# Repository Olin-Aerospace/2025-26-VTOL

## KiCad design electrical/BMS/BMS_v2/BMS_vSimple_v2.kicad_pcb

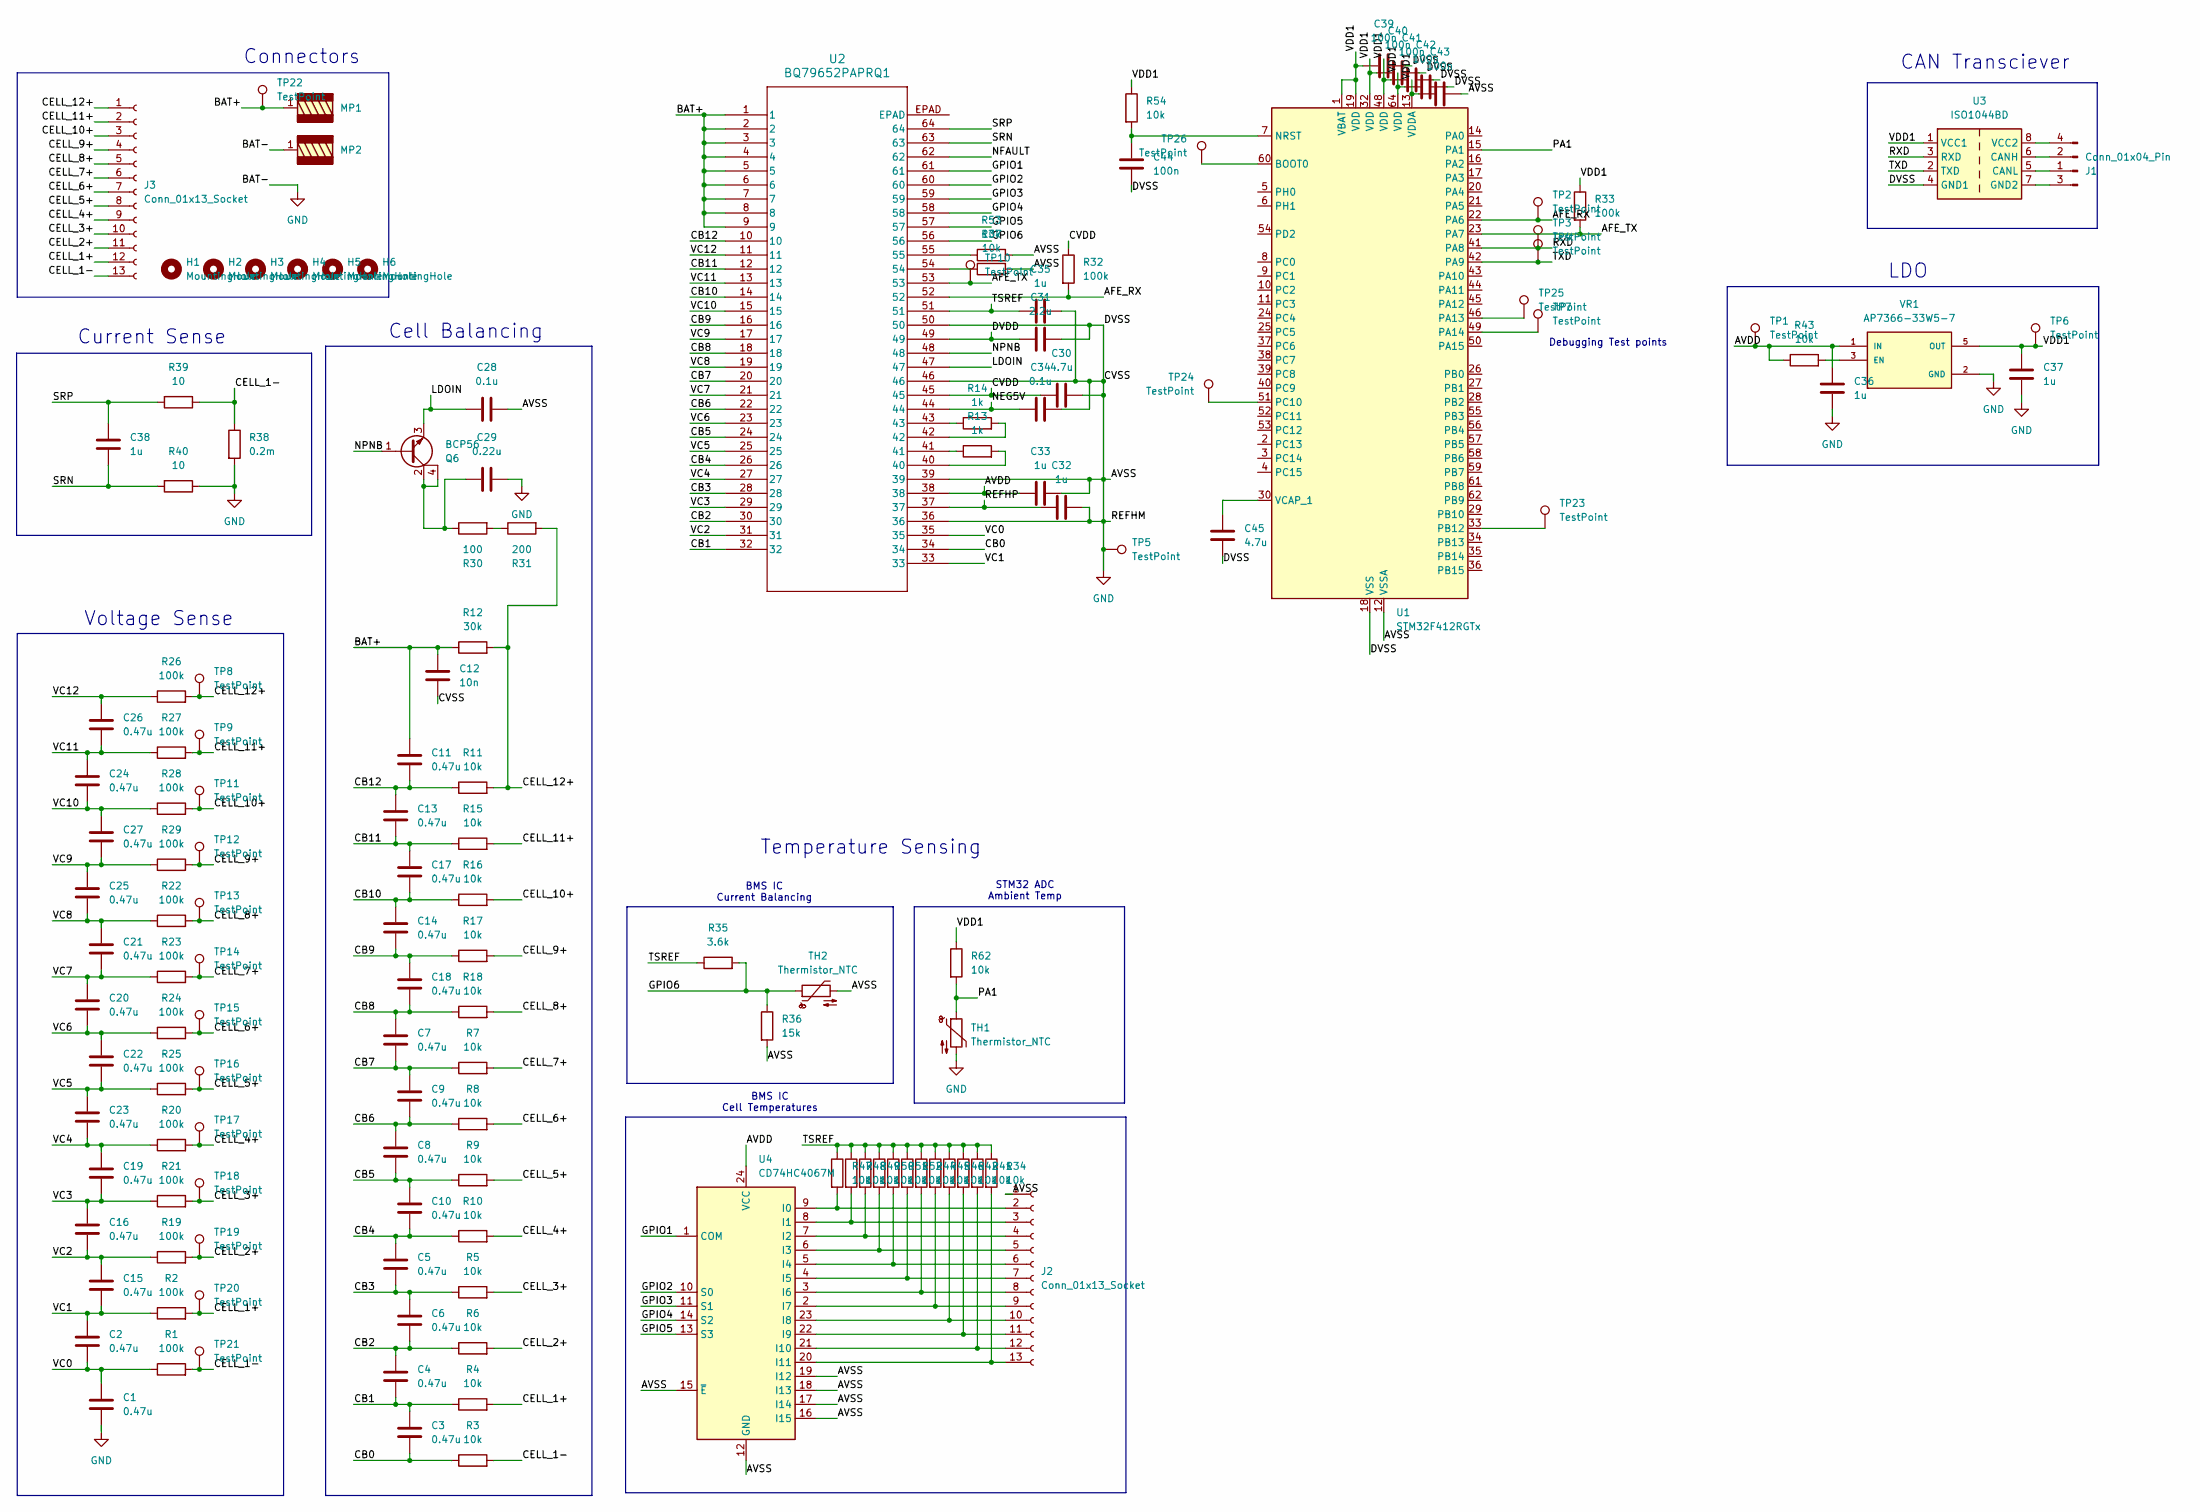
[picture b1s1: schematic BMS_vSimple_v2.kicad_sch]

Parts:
C1, C2, C3, C4, C5, C6, C7, C8, C9, C10, C11, C13, C14, C15, C16, C17, C18, C19, C20, C21, C22, C23, C24, C25, C26, C27: 0.47u; C_0603_1608Metric
C12: 10n; C_0603_1608Metric
C28, C34: 0.1u; C_0603_1608Metric
C29: 0.22u; C_0603_1608Metric
C30, C45: 4.7u; C_0603_1608Metric
C31: 2.2u; C_0603_1608Metric
C32, C33, C35, C36, C37, C38: 1u; C_0603_1608Metric
C39, C40, C41, C42, C43, C44: 100n; C_0603_1608Metric
H1, H2, H3, H4, H5, H6: MountingHole; MountingHole_2.2mm_M2
J1: Conn_01x04_Pin; JST_XH_B4B-XH-A_1x04_P2.50mm_Vertical
J2, J3: Conn_01x13_Socket; JST_XH_B13B-XH-A_1x13_P2.50mm_Vertical
MP1, MP2: 7461117; MP_Wurth_WP-RAFU_7461117; Part Number 7461117
Q6: BCP56; SOT-223-3_TabPin2
R1, R2, R19, R20, R21, R22, R23, R24, R25, R26, R27, R28, R29, R32, R33: 100k; R_0603_1608Metric
R3, R4, R5, R6, R7, R8, R9, R10, R11, R15, R16, R17, R18, R34, R37, R41, R42, R43, R44, R45, R46, R47, R48, R49, R50, R51, R52, R53, R54, R62: 10k; R_0603_1608Metric
R12: 30k; R_0603_1608Metric
R13, R14: 1k; R_0603_1608Metric
R30: 100; R_0603_1608Metric
R31: 200; R_0603_1608Metric
R35: 3.6k; R_0603_1608Metric
R36: 15k; R_0603_1608Metric
R38: 0.2m; RESC15077X200N
R39, R40: 10; R_0603_1608Metric
TH1, TH2: Thermistor_NTC; R_0603_1608Metric
TP1, TP2, TP3, TP4, TP6, TP7, TP10, TP23, TP24, TP25, TP26: TestPoint; TestPoint_Pad_2.0x2.0mm
TP5, TP8, TP9, TP11, TP12, TP13, TP14, TP15, TP16, TP17, TP18, TP19, TP20, TP21, TP22: TestPoint; TestPoint_Bridge_Pitch2.54mm_Drill1.0mm
U1: STM32F412RGTx; LQFP-64_10x10mm_P0.5mm
U2: BQ79652PAPRQ1; QFP_2PAPRQ1_TEX
U3: ISO1044BD; SOIC-8_3.9x4.9mm_P1.27mm
U4: CD74HC4067M; SOIC-24W_7.5x15.4mm_P1.27mm
VR1: AP7366-33W5-7; SOT95P285X140-5N; PARTREV 1-2

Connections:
/AFE_RX: R32.2, TP2.1, U1.22 (PA6), U2.52
/AFE_TX: R33.2, TP10.1, U1.23 (PA7), U2.53
/AVDD: C33.1, C36.1, R43.1, TP1.1, U2.38, U4.24 (VCC), VR1.1 (IN)
/BAT+: C11.1, C12.1, MP1.1, R12.1, TP22.1, U2.1, U2.2, U2.3, U2.4, U2.5, U2.6, U2.7, U2.8, U2.9
/CB0: C3.2, R3.1, U2.34
/CB1: C3.1, C4.2, R4.1, U2.32
/CB2: C4.1, C6.2, R6.1, U2.30
/CB3: C5.2, C6.1, R5.1, U2.28
/CB4: C5.1, C10.2, R10.1, U2.26
/CB5: C8.2, C10.1, R9.1, U2.24
/CB6: C8.1, C9.2, R8.1, U2.22
/CB7: C7.2, C9.1, R7.1, U2.20
/CB8: C7.1, C18.2, R18.1, U2.18
/CB9: C14.2, C18.1, R17.1, U2.16
/CB10: C14.1, C17.2, R16.1, U2.14
/CB11: C13.2, C17.1, R15.1, U2.12
/CB12: C11.2, C13.1, R11.1, U2.10
/CELL_1+: J3.12, R2.2, R4.2, TP20.1
/CELL_1-: J3.13, R1.2, R3.2, R38.1, R39.1, TP21.1
/CELL_2+: J3.11, R6.2, R19.2, TP19.1
/CELL_3+: J3.10, R5.2, R21.2, TP18.1
/CELL_4+: J3.9, R10.2, R20.2, TP17.1
/CELL_5+: J3.8, R9.2, R25.2, TP16.1
/CELL_6+: J3.7, R8.2, R24.2, TP15.1
/CELL_7+: J3.6, R7.2, R23.2, TP14.1
/CELL_8+: J3.5, R18.2, R22.2, TP13.1
/CELL_9+: J3.4, R17.2, R29.2, TP12.1
/CELL_10+: J3.3, R16.2, R28.2, TP11.1
/CELL_11+: J3.2, R15.2, R27.2, TP9.1
/CELL_12+: J3.1, R11.2, R12.2, R26.2, R31.2, TP8.1
/CVDD: C30.1, R32.1, U2.45
/DVDD: C31.1, U2.49
/GPIO1: U2.61, U4.1 (COM)
/GPIO2: U2.60, U4.10 (S0)
/GPIO3: U2.59, U4.11 (S1)
/GPIO4: U2.58, U4.14 (S2)
/GPIO5: U2.57, U4.13 (S3)
/GPIO6: R35.2, R36.1, TH2.1, U2.56
/LDOIN: C28.2, Q6.3 (E), U2.47
/NEG5V: C34.2, U2.44
/NFAULT: U2.62
/NPNB: Q6.1 (B), U2.48
/PA1: R62.2, TH1.1, U1.15 (PA1)
/REFHP: C32.1, U2.37
/RXD: TP3.1, U1.41 (PA8), U3.3 (RXD)
/SRN: C38.2, R40.2, U2.63
/SRP: C38.1, R39.2, U2.64
/TSREF: C35.2, R34.1, R35.1, R41.1, R42.1, R44.1, R45.1, R46.1, R47.1, R48.1, R49.1, R50.1, R51.1, R52.1, U2.51
/TXD: TP4.1, U1.42 (PA9), U3.2 (TXD)
/VC0: C1.1, C2.2, R1.1, U2.35
/VC1: C2.1, C15.2, R2.1, U2.33
/VC2: C15.1, C16.2, R19.1, U2.31
/VC3: C16.1, C19.2, R21.1, U2.29
/VC4: C19.1, C23.2, R20.1, U2.27
/VC5: C22.2, C23.1, R25.1, U2.25
/VC6: C20.2, C22.1, R24.1, U2.23
/VC7: C20.1, C21.2, R23.1, U2.21
/VC8: C21.1, C25.2, R22.1, U2.19
/VC9: C25.1, C27.2, R29.1, U2.17
/VC10: C24.2, C27.1, R28.1, U2.15
/VC11: C24.1, C26.2, R27.1, U2.13
/VC12: C26.1, R26.1, U2.11
/VDD1: C37.1, C39.1, C40.1, C41.1, C42.1, C43.1, R33.1, R54.1, R62.1, TP6.1, U1.1 (VBAT), U1.13 (VDDA), U1.19 (VDD), U1.32 (VDD), U1.48 (VDD), U1.64 (VDD), U3.1 (VCC1), VR1.5 (OUT)
GND: C1.2, C12.2, C28.1, C29.2, C30.2, C31.2, C32.2, C33.2, C34.1, C35.1, C36.2, C37.2, C39.2, C40.2, C41.2, C42.2, C43.2, C44.2, C45.2, J2.1, MP2.1, R36.2, R37.2, R38.2, R40.1, R53.2, TH1.2, TH2.2, TP5.1, U1.12 (VSSA), U1.18 (VSS), U1.31 (VSS), U1.47 (VSS), U1.63 (VSS), U2.36, U2.39, U2.46, U2.50, U3.4 (GND1), U4.12 (GND), U4.15 (~E), U4.16 (I15), U4.17 (I14), U4.18 (I13), U4.19 (I12), VR1.2 (GND)
unnamed: C29.1, Q6.2 (C), Q6.4 (C), R30.1
unnamed: J1.1, U3.5 (CANL)
unnamed: J1.2, U3.6 (CANH)
unnamed: J1.3, U3.7 (GND2)
unnamed: J1.4, U3.8 (VCC2)
unnamed: J2.2, R47.2, U4.9 (I0)
unnamed: J2.3, R48.2, U4.8 (I1)
unnamed: J2.4, R49.2, U4.7 (I2)
unnamed: J2.5, R50.2, U4.6 (I3)
unnamed: J2.6, R51.2, U4.5 (I4)
unnamed: J2.7, R52.2, U4.4 (I5)
unnamed: J2.8, R44.2, U4.3 (I6)
unnamed: J2.9, R45.2, U4.2 (I7)
unnamed: J2.10, R46.2, U4.23 (I8)
unnamed: J2.11, R42.2, U4.22 (I9)
unnamed: J2.12, R41.2, U4.21 (I10)
unnamed: J2.13, R34.2, U4.20 (I11)
unnamed: R13.1, U2.41
unnamed: R13.2, U2.40
unnamed: R14.1, U2.43
unnamed: R14.2, U2.42
unnamed: R30.2, R31.1
unnamed: R37.1, U2.54
unnamed: R53.1, U2.55
unnamed: TP26.1, U1.60 (BOOT0)
unnamed: C44.1, R54.2, U1.7 (NRST)
unnamed: TP25.1, U1.46 (PA13)
unnamed: TP7.1, U1.49 (PA14)
unnamed: TP23.1, U1.33 (PB12)
unnamed: TP24.1, U1.51 (PC10)
unnamed: C45.1, U1.30 (VCAP_1)
unnamed: R43.2, VR1.3 (EN)

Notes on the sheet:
Voltage Sense
Current Sense
BMS IC Current Balancing
BMS IC Cell Temperatures
CAN Transciever
Debugging Test points
Cell Balancing
Temperature Sensing
LDO
Connectors
STM32 ADC Ambient Temp

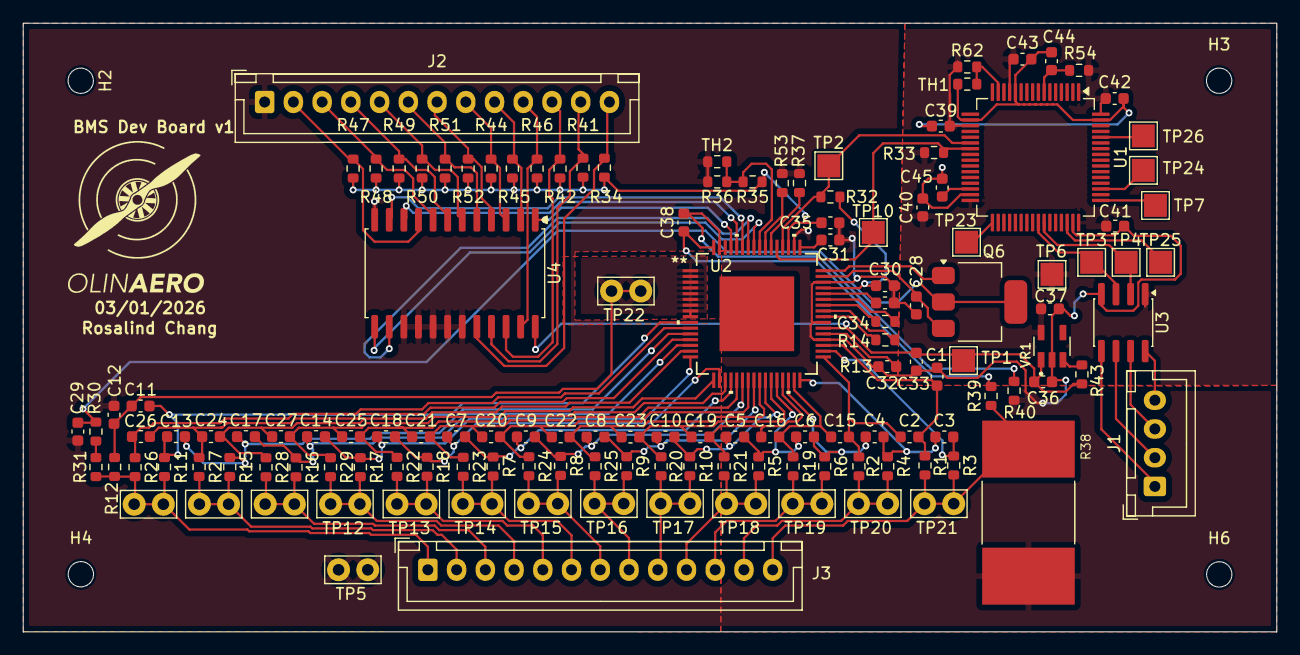
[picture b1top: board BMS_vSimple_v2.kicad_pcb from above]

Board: 4 copper layers, 109.0 x 52.9 mm, 141 parts (0 on the bottom side), 95 nets.

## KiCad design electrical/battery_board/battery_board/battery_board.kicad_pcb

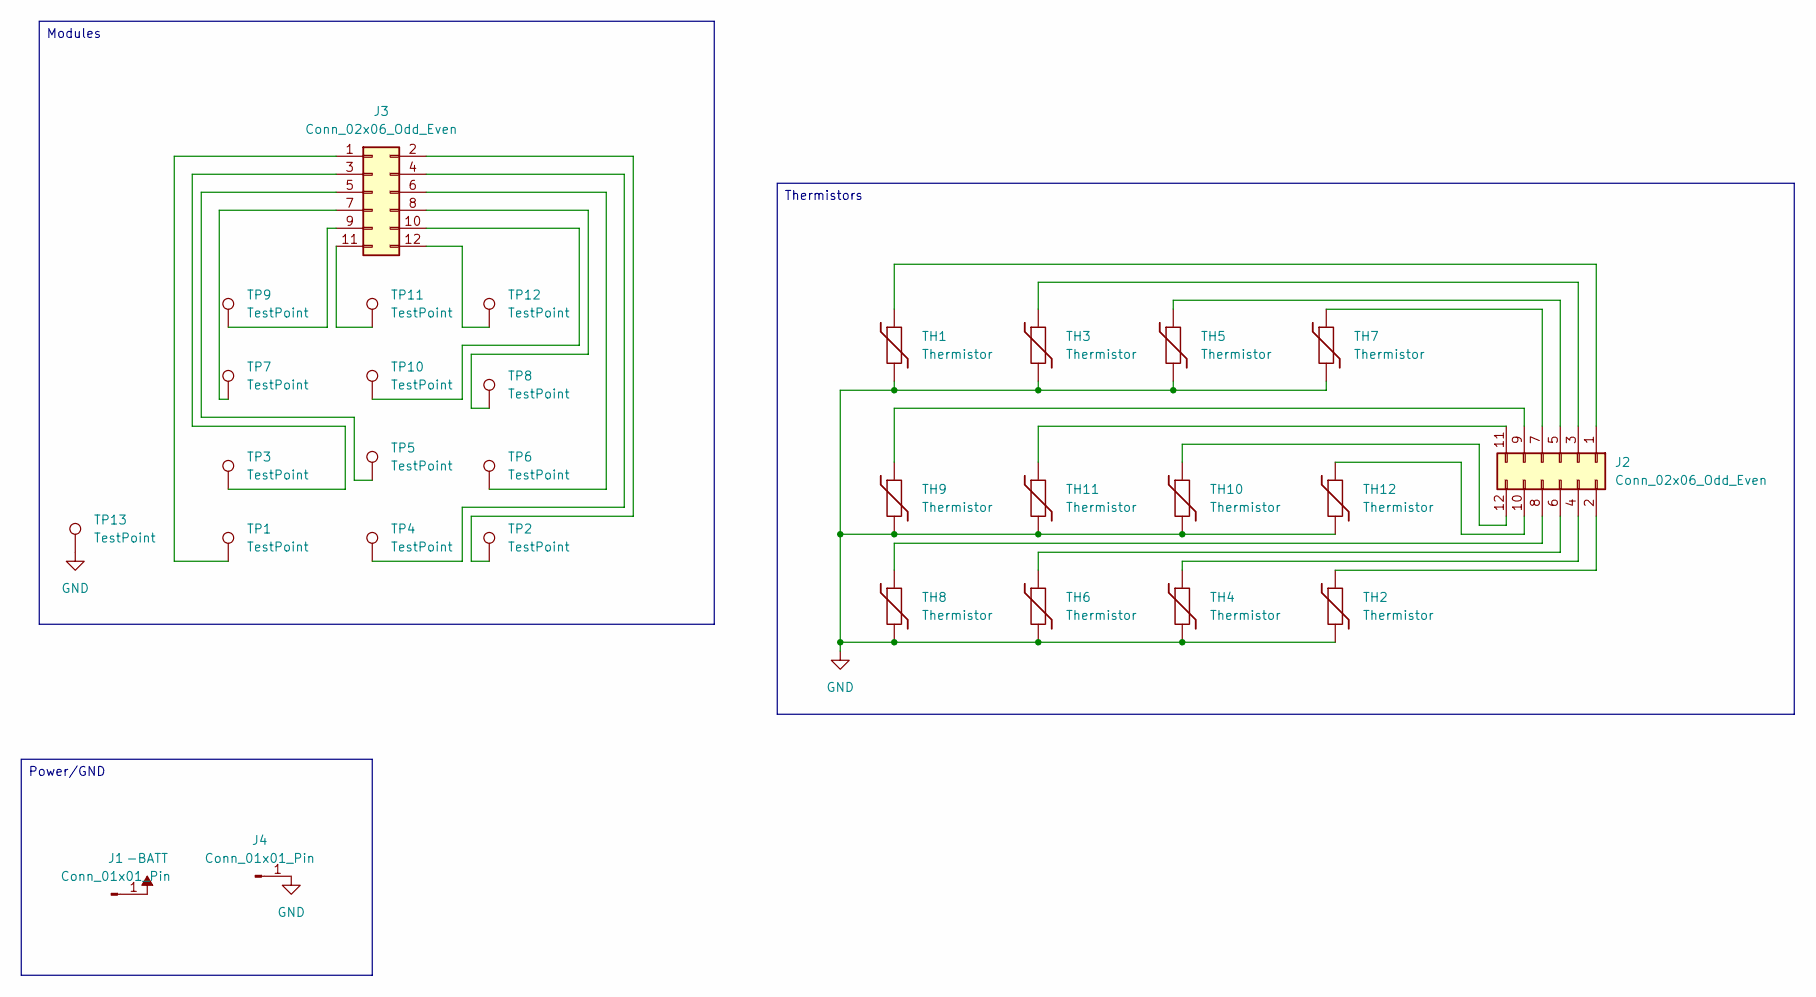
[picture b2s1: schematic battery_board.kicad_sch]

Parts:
J1, J4: Conn_01x01_Pin; MP_Wurth_WP-RAFU_7461117
J2, J3: Conn_02x06_Odd_Even; PinHeader_2x06_P2.54mm_Vertical
TH1, TH2, TH3, TH4, TH5, TH6, TH7, TH8, TH9, TH10, TH11, TH12: Thermistor; R_0603_1608Metric
TP1, TP2, TP3, TP4, TP5, TP6, TP7, TP8, TP9, TP10, TP11, TP12, TP13: TestPoint; TestPoint_Keystone_5019_Miniature

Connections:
-BATT: J1.1
GND: J4.1, TH1.2, TH2.2, TH3.2, TH4.2, TH5.2, TH6.2, TH7.2, TH8.2, TH9.2, TH10.2, TH11.2, TH12.2, TP13.1
unnamed: J2.1, TH1.1
unnamed: J2.2, TH2.1
unnamed: J2.3, TH3.1
unnamed: J2.4, TH4.1
unnamed: J2.5, TH5.1
unnamed: J2.6, TH6.1
unnamed: J2.7, TH7.1
unnamed: J2.8, TH8.1
unnamed: J2.9, TH9.1
unnamed: J2.10, TH12.1
unnamed: J2.11, TH11.1
unnamed: J2.12, TH10.1
unnamed: J3.1, TP1.1
unnamed: J3.2, TP2.1
unnamed: J3.3, TP3.1
unnamed: J3.4, TP4.1
unnamed: J3.5, TP5.1
unnamed: J3.6, TP6.1
unnamed: J3.7, TP7.1
unnamed: J3.8, TP8.1
unnamed: J3.9, TP9.1
unnamed: J3.10, TP10.1
unnamed: J3.11, TP11.1
unnamed: J3.12, TP12.1

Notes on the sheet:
Power/GND
Thermistors
Modules

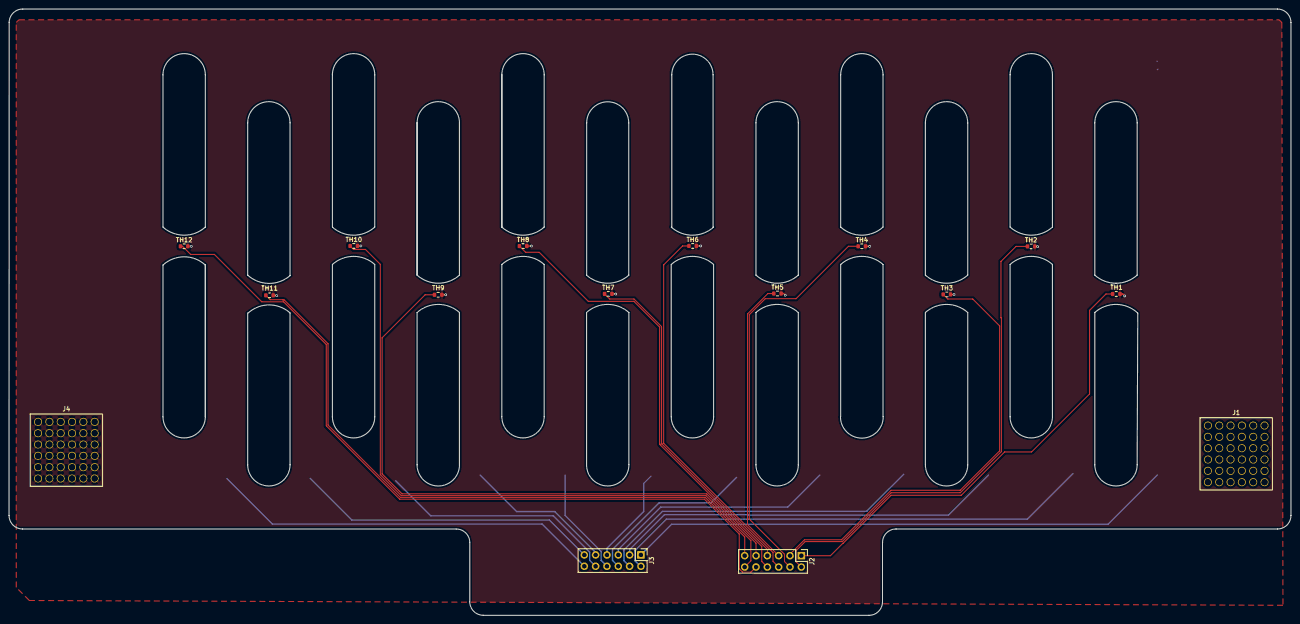
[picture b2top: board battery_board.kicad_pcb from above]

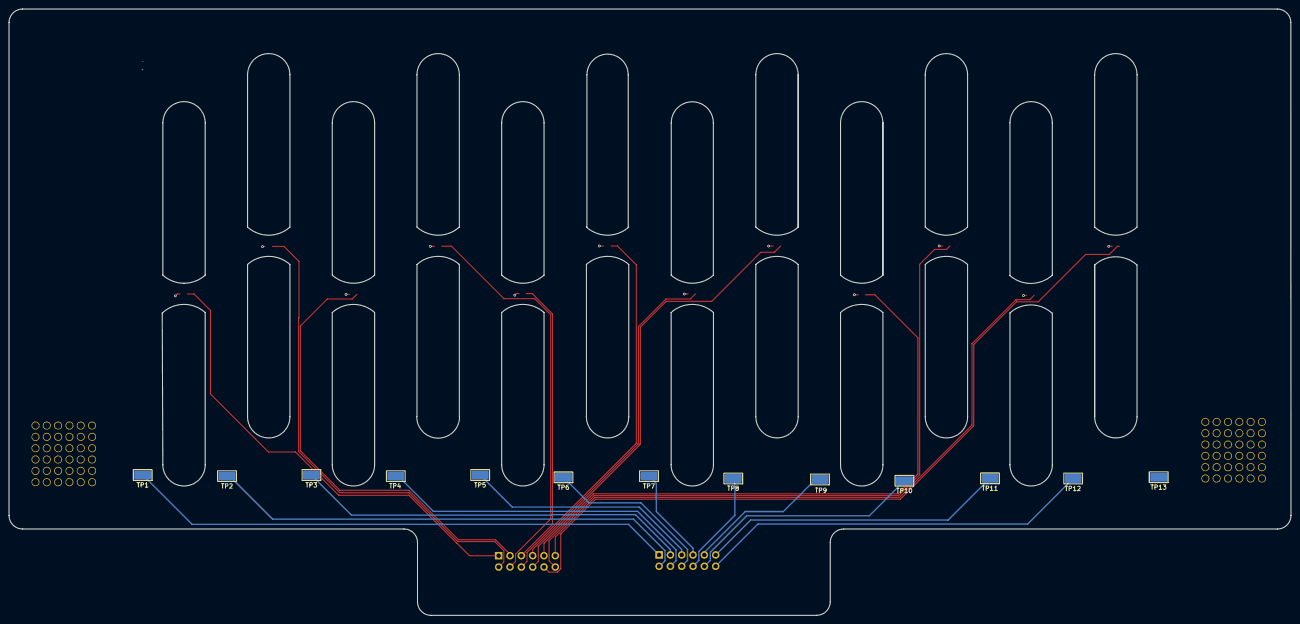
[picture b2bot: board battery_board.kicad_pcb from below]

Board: 2 copper layers, 287.5 x 136.0 mm, 29 parts (13 on the bottom side), 25 nets.

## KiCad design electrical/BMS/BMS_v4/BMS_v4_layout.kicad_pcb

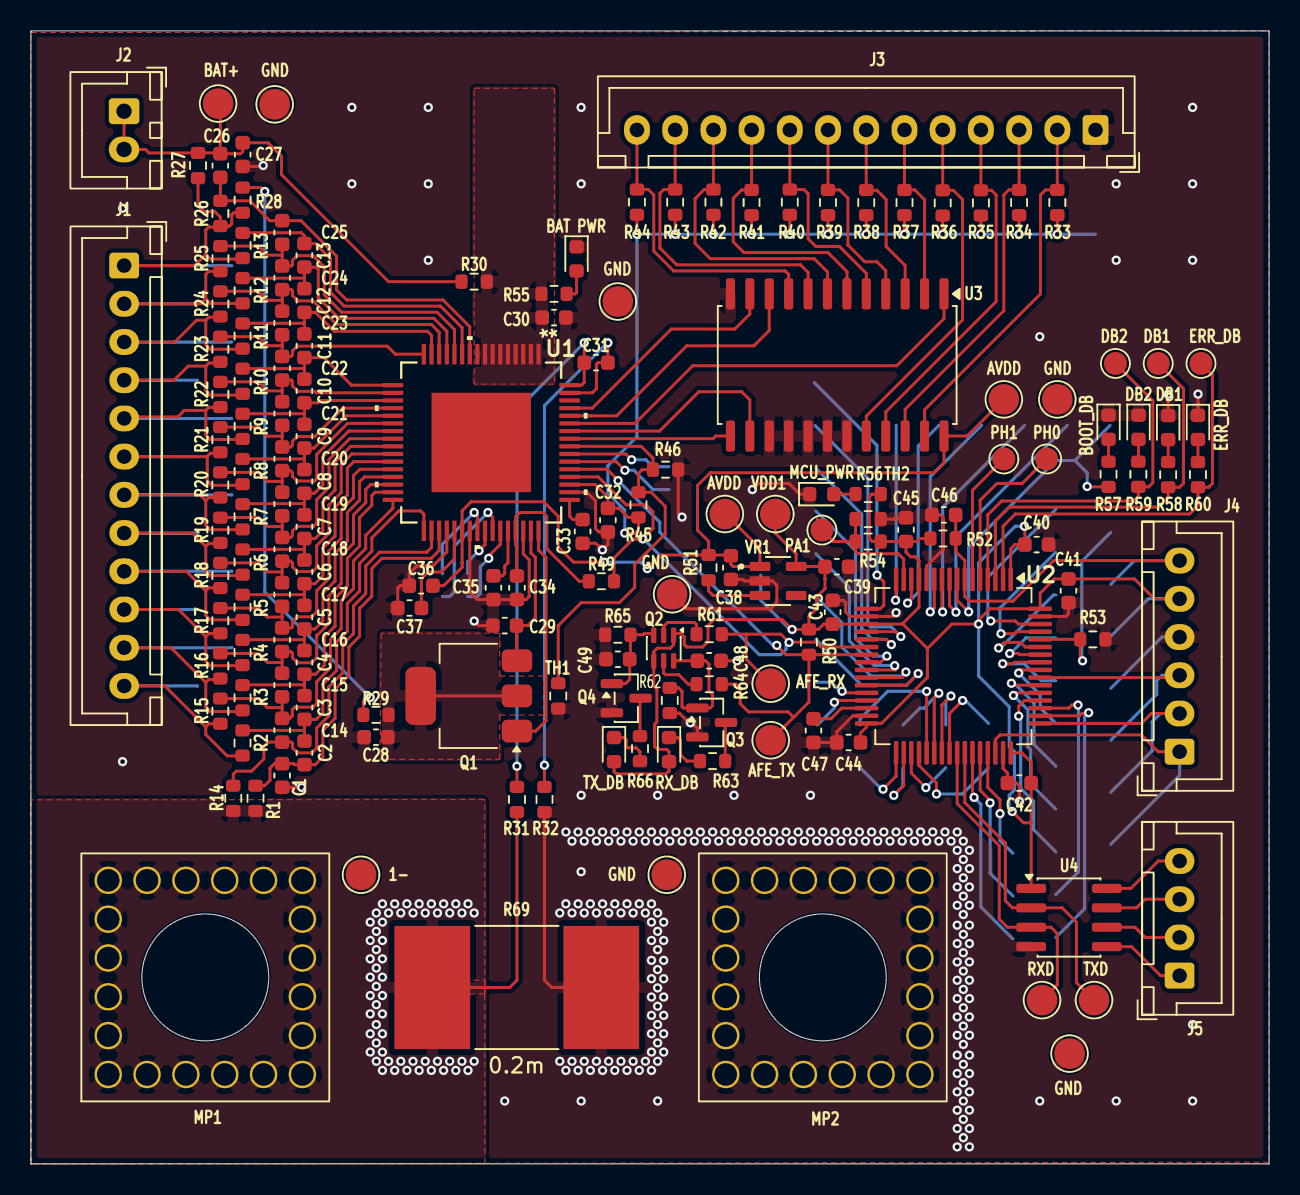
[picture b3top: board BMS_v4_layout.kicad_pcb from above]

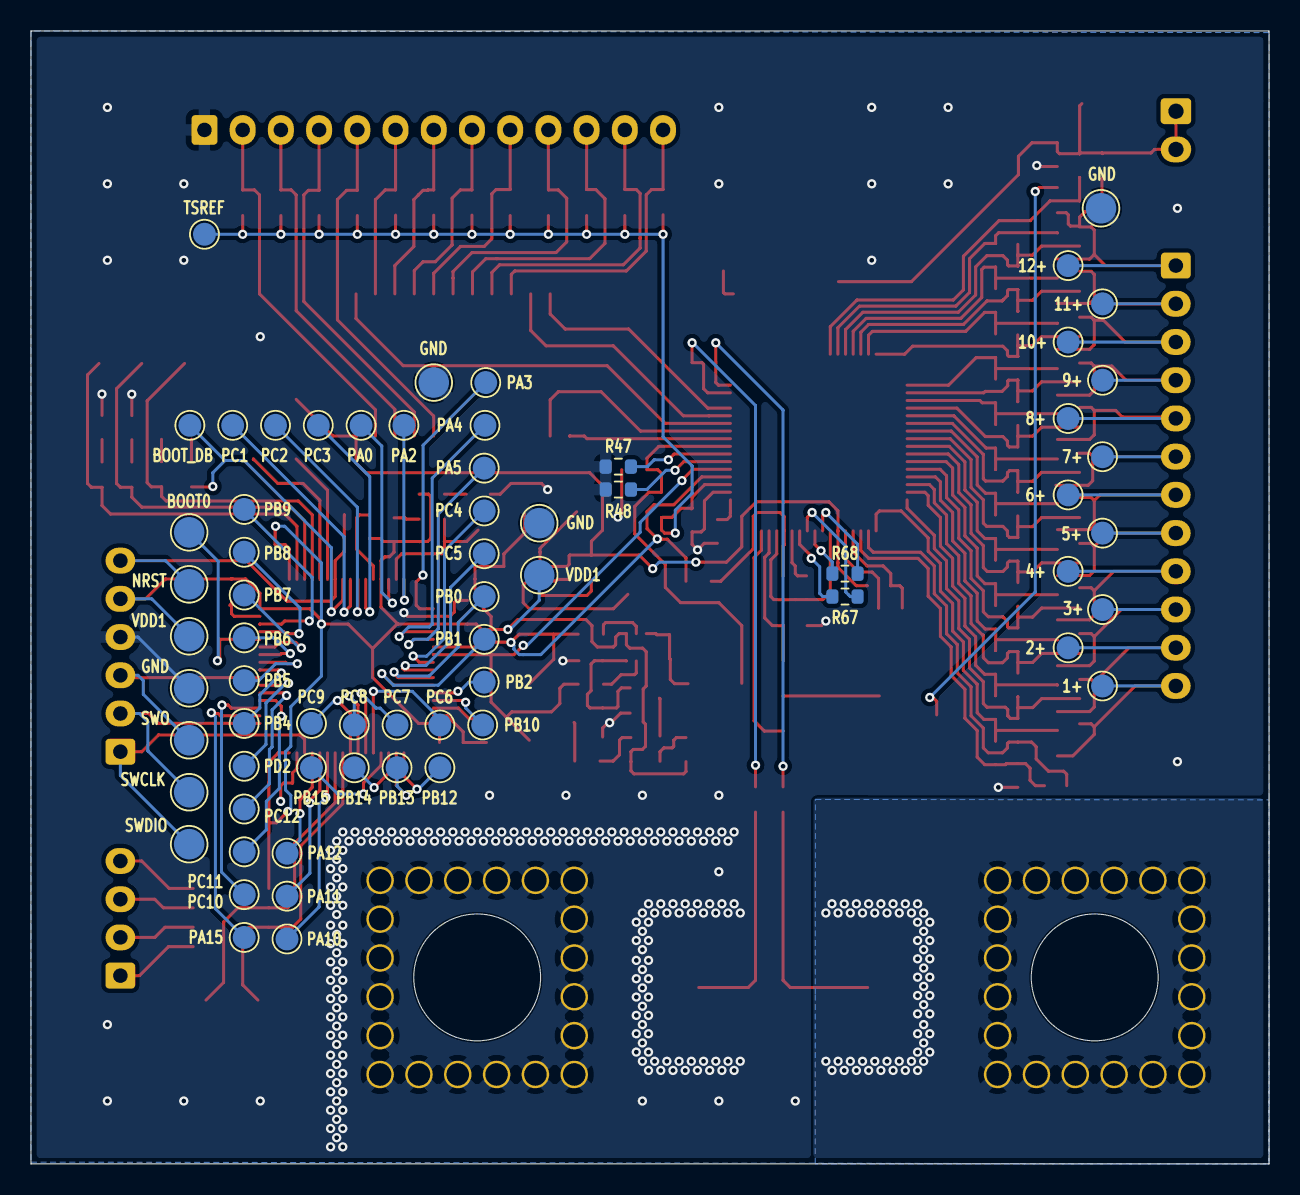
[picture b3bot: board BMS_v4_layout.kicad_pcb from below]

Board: 4 copper layers, 81.0 x 74.1 mm, 232 parts (65 on the bottom side), 151 nets.

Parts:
1+, 2+, 3+, 4+, 5+, 6+, 7+, 8+, 9+, 10+, 11+, 12+: TestPoint; TestPoint_Pad_D1.5mm
1-: TestPoint; TestPoint_Pad_D2.0mm
AFE_RX: TestPoint; TestPoint_Pad_D2.0mm
AFE_TX: TestPoint; TestPoint_Pad_D2.0mm
AVDD: TestPoint; TestPoint_Pad_D2.0mm
AVDD#2: TestPoint; TestPoint_Pad_D2.0mm
BAT PWR: LED; LED_0603_1608Metric
BAT+: TestPoint; TestPoint_Pad_D2.0mm
BOOT0: TestPoint; TestPoint_Pad_D2.0mm
BOOT_DB: LED; LED_0603_1608Metric
BOOT_DB#2: TestPoint; TestPoint_Pad_D1.5mm
C1, C2, C3, C4, C5, C6, C7, C8, C9, C10, C11, C12, C13, C14, C15, C16, C17, C18, C19, C20, C21, C22, C23, C24, C25, C26: 0.47u; C_0603_1608Metric
C27, C30: 10n; C_0603_1608Metric
C28: 0.22u; C_0603_1608Metric
C29, C35: 0.1u; C_0603_1608Metric
C31, C32, C36, C37, C38, C39: 1u; C_0603_1608Metric
C33: 2.2u; C_0603_1608Metric
C34, C47: 4.7u; C_0603_1608Metric
C40, C41, C42, C43, C44, C45, C46: 100n; C_0603_1608Metric
C48, C49: 22n; C_0603_1608Metric
DB1, DB2: TestPoint; TestPoint_Pad_D1.5mm
DB1#2, DB2#2: LED; LED_0603_1608Metric
ERR_DB: LED; LED_0603_1608Metric
ERR_DB#2: TestPoint; TestPoint_Pad_D1.5mm
GND: TestPoint; TestPoint_Pad_D2.0mm
GND#2, GND#3, GND#4, GND#5, GND#6, GND#7, GND#8, GND#9, GND#10: TestPoint; TestPoint_Pad_D2.0mm
H1, H2, H3, H4, H5, H6: MountingHole; MountingHole_2.2mm_M2
J1: Conn_01x12_Socket; JST_XH_B12B-XH-A_1x12_P2.50mm_Vertical
J2: Conn_01x02_Socket; JST_XH_B2B-XH-A_1x02_P2.50mm_Vertical
J3: Conn_01x13_Socket; JST_XH_B13B-XH-A_1x13_P2.50mm_Vertical
J4: Conn_01x06_Pin; JST_XH_B6B-XH-A_1x06_P2.50mm_Vertical
J5: Conn_01x04_Pin; JST_XH_B4B-XH-A_1x04_P2.50mm_Vertical
MCU_PWR: LED; LED_0603_1608Metric
MP1, MP2: 7461090; MP_Wurth_WP-BUCF_7461090
NRST: TestPoint; TestPoint_Pad_D2.0mm
PA0, PA1, PA2, PA3, PA4, PA5, PA10, PA11, PA12, PA15: TestPoint; TestPoint_Pad_D1.5mm
PB0, PB1, PB2, PB4, PB5, PB6, PB7, PB8, PB9, PB10, PB12, PB13, PB14, PB15: TestPoint; TestPoint_Pad_D1.5mm
PC1, PC2, PC3, PC4, PC5, PC6, PC7, PC8, PC9, PC10, PC11, PC12: TestPoint; TestPoint_Pad_D1.5mm
PD2: TestPoint; TestPoint_Pad_D1.5mm
PH0, PH1: TestPoint; TestPoint_Pad_D1.5mm
Q1: BCP56; SOT-223
Q2: BC857BS; SOT-363_SC-70-6
Q3, Q4: T2N7002AK; SOT-23
R1, R2, R3, R4, R5, R6, R7, R8, R9, R10, R11, R12, R13, R14, R15, R16, R17, R18, R19, R20, R21, R22, R23, R24, R25, R26, R29: 100; R_0603_1608Metric
R27: 30k; R_0603_1608Metric
R28: 200; R_0603_1608Metric
R30: 30; R_0603_1608Metric
R31, R32: 10; R_0603_1608Metric
R33, R34, R35, R36, R37, R38, R39, R40, R41, R42, R43, R44, R47, R48, R51, R52, R53, R54: 10k; R_0603_1608Metric
R45: 3.6k; R_0603_1608Metric
R46: 15k; R_0603_1608Metric
R49, R50: 100k; R_0603_1608Metric
R55: 4.7k; R_0603_1608Metric
R56, R57, R58, R59, R60, R61, R64, R67, R68: 1k; R_0603_1608Metric
R62, R65: 1M; R_0603_1608Metric
R63, R66: 120; R_0603_1608Metric
R69: 0.2m; RESC15077X200N
RXD: TestPoint; TestPoint_Pad_D2.0mm
RX_DB: LED; LED_0603_1608Metric
SWCLK: TestPoint; TestPoint_Pad_D2.0mm
SWDIO: TestPoint; TestPoint_Pad_D2.0mm
SWO: TestPoint; TestPoint_Pad_D2.0mm
TH1, TH2: Thermistor_NTC; R_0603_1608Metric
TSREF: TestPoint; TestPoint_Pad_D1.5mm
TXD: TestPoint; TestPoint_Pad_D2.0mm
TX_DB: LED; LED_0603_1608Metric
U1: BQ79652PAPRQ1; QFP_2PAPRQ1_TEX
U2: STM32F412RGTx; LQFP-64_10x10mm_P0.5mm
U3: CD74HC4067M; SOIC-24W_7.5x15.4mm_P1.27mm
U4: ISO1044BD; SOIC-8_3.9x4.9mm_P1.27mm
VDD1, VDD1#2, VDD1#3: TestPoint; TestPoint_Pad_D2.0mm
VR1: AP7366-33W5-7; SOT95P285X140-5N

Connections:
/AFE_POWER_DEBUG: C30.1, R30.2, R55.1, U1.1, U1.2, U1.3, U1.4, U1.5, U1.6, U1.7, U1.8, U1.9
/AFE_RX: AFE_RX.1 (1_1), R49.2, R61.1, U1.52, U2.22 (PA6)
/AFE_TX: AFE_TX.1 (1_1), R50.2, R64.1, U1.53, U2.23 (PA7)
/AVDD: AVDD.1 (1_1), AVDD#2.1 (1_1), C36.1, C38.1, R51.1, U1.38, U3.24 (VCC), VR1.1 (IN)
/BAT+: BAT+.1 (1_1), C26.1, C27.1, J2.1, J2.2, R27.1, R30.1
/BOOT_DEBUG: BOOT_DB#2.1 (1_1), R57.1, U2.8 (PC0)
/CB0: C14.2, R14.1, U1.34
/CB1: C14.1, C15.2, R15.1, U1.32
/CB2: C15.1, C16.2, R16.1, U1.30
/CB3: C16.1, C17.2, R17.1, U1.28
/CB4: C17.1, C18.2, R18.1, U1.26
/CB5: C18.1, C19.2, R19.1, U1.24
/CB6: C19.1, C20.2, R20.1, U1.22
/CB7: C20.1, C21.2, R21.1, U1.20
/CB8: C21.1, C22.2, R22.1, U1.18
/CB9: C22.1, C23.2, R23.1, U1.16
/CB10: C23.1, C24.2, R24.1, U1.14
/CB11: C24.1, C25.2, R25.1, U1.12
/CB12: C25.1, C26.2, R26.1, U1.10
/CELL_1+: 1+.1 (1_1), J1.12, R2.2, R15.2
/CELL_1-: 1-.1 (1_1), MP1.1 (1_1), R1.2, R14.2, R31.1, R69.1
/CELL_2+: 2+.1 (1_1), J1.11, R3.2, R16.2
/CELL_3+: 3+.1 (1_1), J1.10, R4.2, R17.2
/CELL_4+: 4+.1 (1_1), J1.9, R5.2, R18.2
/CELL_5+: 5+.1 (1_1), J1.8, R6.2, R19.2
/CELL_6+: 6+.1 (1_1), J1.7, R7.2, R20.2
/CELL_7+: 7+.1 (1_1), J1.6, R8.2, R21.2
/CELL_8+: 8+.1 (1_1), J1.5, R9.2, R22.2
/CELL_9+: 9+.1 (1_1), J1.4, R10.2, R23.2
/CELL_10+: 10+.1 (1_1), J1.3, R11.2, R24.2
/CELL_11+: 11+.1 (1_1), J1.2, R12.2, R25.2
/CELL_12+: 12+.1 (1_1), J1.1, R13.2, R26.2, R27.2, R28.2
/CVDD: C34.1, R49.1, U1.45
/DVDD: C33.1, U1.49
/ERROR_DEBUG: ERR_DB#2.1 (1_1), R60.1, U2.2 (PC13)
/GENERAL_DEBUG_1: DB1.1 (1_1), R58.1, U2.3 (PC14)
/GENERAL_DEBUG_2: DB2.1 (1_1), R59.1, U2.4 (PC15)
/GPIO1: U1.61, U3.11 (S1)
/GPIO2: U1.60, U3.10 (S0)
/GPIO3: U1.59, U3.1 (COM)
/GPIO4: U1.58, U3.14 (S2)
/GPIO5: U1.57, U3.13 (S3)
/GPIO6: R45.2, R46.1, TH1.1, U1.56
/LDOIN: C29.2, Q1.3 (E), U1.47
/NEG5V: C35.2, U1.44
/NPNB: Q1.1 (B), U1.48
/NRST: C46.1, J4.6, NRST.1 (1_1), R52.2, U2.7 (NRST)
/PA1: PA1.1 (1_1), R54.2, TH2.1, U2.15 (PA1)
/REFHP: C37.1, U1.37
/RXD: RXD.1 (1_1), U2.41 (PA8), U4.3 (RXD)
/SRN: C31.2, R32.2, U1.63
/SRP: C31.1, R31.2, U1.64
/SWCLK: J4.2, SWCLK.1 (1_1), U2.49 (PA14)
/SWDIO: J4.1, SWDIO.1 (1_1), U2.46 (PA13)
/SWO: J4.3, SWO.1 (1_1), U2.55 (PB3)
/TSREF: C32.2, R33.1, R34.1, R35.1, R36.1, R37.1, R38.1, R39.1, R40.1, R41.1, R42.1, R43.1, R44.1, R45.1, TSREF.1 (1_1), U1.51
/TXD: TXD.1 (1_1), U2.42 (PA9), U4.2 (TXD)
/VC0: C1.1, C2.2, R1.1, U1.35
/VC1: C2.1, C3.2, R2.1, U1.33
/VC2: C3.1, C4.2, R3.1, U1.31
/VC3: C4.1, C5.2, R4.1, U1.29
/VC4: C5.1, C6.2, R5.1, U1.27
/VC5: C6.1, C7.2, R6.1, U1.25
/VC6: C7.1, C8.2, R7.1, U1.23
/VC7: C8.1, C9.2, R8.1, U1.21
/VC8: C9.1, C10.2, R9.1, U1.19
/VC9: C10.1, C11.2, R10.1, U1.17
/VC10: C11.1, C12.2, R11.1, U1.15
/VC11: C12.1, C13.2, R12.1, U1.13
/VC12: C13.1, R13.1, U1.11
/VDD1: C39.1, C40.1, C41.1, C42.1, C43.1, C44.1, C45.1, J4.5, Q2.1 (E1), Q2.4 (E2), R50.1, R52.1, R54.1, R56.1, RX_DB.2 (A), TX_DB.2 (A), U2.1 (VBAT), U2.13 (VDDA), U2.19 (VDD), U2.32 (VDD), U2.48 (VDD), U2.64 (VDD), U4.1 (VCC1), VDD1.1 (1_1), VDD1#2.1 (1_1), VDD1#3.1 (1_1), VR1.5 (OUT)
GND: BAT PWR.1 (K), BOOT_DB.1 (K), C1.2, C27.2, C28.2, C29.1, C30.2, C32.1, C33.2, C34.2, C35.1, C36.2, C37.2, C38.2, C39.2, C40.2, C41.2, C42.2, C43.2, C44.2, C45.2, C46.2, C47.2, C48.2, C49.2, DB1#2.1 (K), DB2#2.1 (K), ERR_DB.1 (K), GND.1 (1_1), GND#2.1 (1_1), GND#3.1 (1_1), GND#4.1 (1_1), GND#5.1 (1_1), GND#6.1 (1_1), GND#7.1 (1_1), GND#8.1 (1_1), GND#9.1 (1_1), GND#10.1 (1_1), J3.1, J4.4, MCU_PWR.1 (K), MP2.1 (1_1), Q3.2 (S), Q4.2 (S), R32.1, R46.2, R47.2, R48.2, R53.2, R62.2, R65.2, R69.2, TH1.2, TH2.2, U1.36, U1.39, U1.46, U1.50, U2.12 (VSSA), U2.18 (VSS), U2.31 (VSS), U2.47 (VSS), U2.63 (VSS), U3.12 (GND), U3.15 (~E), U3.16 (I15), U3.17 (I14), U3.18 (I13), U3.19 (I12), U4.4 (GND1), VR1.2 (GND)
unnamed: C28.1, Q1.2 (C), Q1.4 (C), R29.1
unnamed: BAT PWR.2 (A), R55.2
unnamed: MCU_PWR.2 (A), R56.2
unnamed: BOOT_DB.2 (A), R57.2
unnamed: DB1#2.2 (A), R58.2
unnamed: DB2#2.2 (A), R59.2
unnamed: ERR_DB.2 (A), R60.2
unnamed: R63.1, RX_DB.1 (K)
unnamed: R66.1, TX_DB.1 (K)
unnamed: J3.2, R33.2, U3.23 (I8)
unnamed: J3.3, R34.2, U3.22 (I9)
unnamed: J3.4, R35.2, U3.21 (I10)
unnamed: J3.5, R36.2, U3.20 (I11)
unnamed: J3.6, R37.2, U3.2 (I7)
unnamed: J3.7, R38.2, U3.3 (I6)
unnamed: J3.8, R39.2, U3.4 (I5)
unnamed: J3.9, R40.2, U3.5 (I4)
unnamed: J3.10, R41.2, U3.6 (I3)
unnamed: J3.11, R42.2, U3.7 (I2)
unnamed: J3.12, R43.2, U3.8 (I1)
unnamed: J3.13, R44.2, U3.9 (I0)
unnamed: J5.1, U4.5 (CANL)
unnamed: J5.2, U4.6 (CANH)
unnamed: J5.3, U4.7 (GND2)
unnamed: J5.4, U4.8 (VCC2)
unnamed: Q2.2 (B1), R61.2
unnamed: C48.1, Q2.6 (C1), Q3.1 (G), R62.1
unnamed: Q2.5 (B2), R64.2
unnamed: C49.1, Q2.3 (C2), Q4.1 (G), R65.1
unnamed: Q3.3 (D), R63.2
unnamed: Q4.3 (D), R66.2
unnamed: R28.1, R29.2
unnamed: R47.1, U1.55
unnamed: R48.1, U1.54
unnamed: R67.1, U1.43
unnamed: R67.2, U1.42
unnamed: R68.1, U1.41
unnamed: R68.2, U1.40
unnamed: BOOT0.1 (1_1), R53.1, U2.60 (BOOT0)
unnamed: PA0.1 (1_1), U2.14 (PA0)
unnamed: PA2.1 (1_1), U2.16 (PA2)
unnamed: PA3.1 (1_1), U2.17 (PA3)
unnamed: PA4.1 (1_1), U2.20 (PA4)
unnamed: PA5.1 (1_1), U2.21 (PA5)
unnamed: PA10.1 (1_1), U2.43 (PA10)
unnamed: PA11.1 (1_1), U2.44 (PA11)
unnamed: PA12.1 (1_1), U2.45 (PA12)
unnamed: PA15.1 (1_1), U2.50 (PA15)
unnamed: PB0.1 (1_1), U2.26 (PB0)
unnamed: PB1.1 (1_1), U2.27 (PB1)
unnamed: PB2.1 (1_1), U2.28 (PB2)
unnamed: PB4.1 (1_1), U2.56 (PB4)
unnamed: PB5.1 (1_1), U2.57 (PB5)
unnamed: PB6.1 (1_1), U2.58 (PB6)
unnamed: PB7.1 (1_1), U2.59 (PB7)
unnamed: PB8.1 (1_1), U2.61 (PB8)
unnamed: PB9.1 (1_1), U2.62 (PB9)
unnamed: PB10.1 (1_1), U2.29 (PB10)
unnamed: PB12.1 (1_1), U2.33 (PB12)
unnamed: PB13.1 (1_1), U2.34 (PB13)
unnamed: PB14.1 (1_1), U2.35 (PB14)
unnamed: PB15.1 (1_1), U2.36 (PB15)
unnamed: PC1.1 (1_1), U2.9 (PC1)
unnamed: PC2.1 (1_1), U2.10 (PC2)
unnamed: PC3.1 (1_1), U2.11 (PC3)
unnamed: PC4.1 (1_1), U2.24 (PC4)
unnamed: PC5.1 (1_1), U2.25 (PC5)
unnamed: PC6.1 (1_1), U2.37 (PC6)
unnamed: PC7.1 (1_1), U2.38 (PC7)
unnamed: PC8.1 (1_1), U2.39 (PC8)
unnamed: PC9.1 (1_1), U2.40 (PC9)
unnamed: PC10.1 (1_1), U2.51 (PC10)
unnamed: PC11.1 (1_1), U2.52 (PC11)
unnamed: PC12.1 (1_1), U2.53 (PC12)
unnamed: PD2.1 (1_1), U2.54 (PD2)
unnamed: PH0.1 (1_1), U2.5 (PH0)
unnamed: PH1.1 (1_1), U2.6 (PH1)
unnamed: C47.1, U2.30 (VCAP_1)
unnamed: R51.2, VR1.3 (EN)

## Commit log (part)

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2025-12-03 Added software readme
2025-12-04 cell balancing circuitry
2025-12-04 voltage sense circuitry
2025-12-04 grounding
2025-12-05 temperature sensing for pcb and mosfet
2025-12-13 LDO from AFE 5V to MCU 3V3
2025-12-16 current sensing + changed AFE to BQ79652
2026-01-29 oops most updated version ig (please check if my connectors are ok (i don't have a sense of direction), also i know one of them should be going on the back of the PCB)
2026-02-02 changing approach to stitching
2026-02-06 progress, also added footprints for redcube
2026-02-06 adding simpler layout without gate driver
2026-02-07 created ros2ws and added my arming node. I have not tested the arming node yet
2026-02-07 testing somthing
2026-02-10 Partially complete schematic and layout
2026-02-12 making arming node work
2026-02-18 added takeoff node
2026-02-18 takeoff node is wrong
2026-02-18 fixed nodes
2026-02-18 updated pcb
2026-02-19 adding mounting holes and finalizing dimensions
2026-02-25 bms is smaller now...
2026-02-27 bms pcb layout v2
2026-03-01 revised BMS, ty Joseph for feedback :D
2026-04-28 latest BMS board, silkscreen done
